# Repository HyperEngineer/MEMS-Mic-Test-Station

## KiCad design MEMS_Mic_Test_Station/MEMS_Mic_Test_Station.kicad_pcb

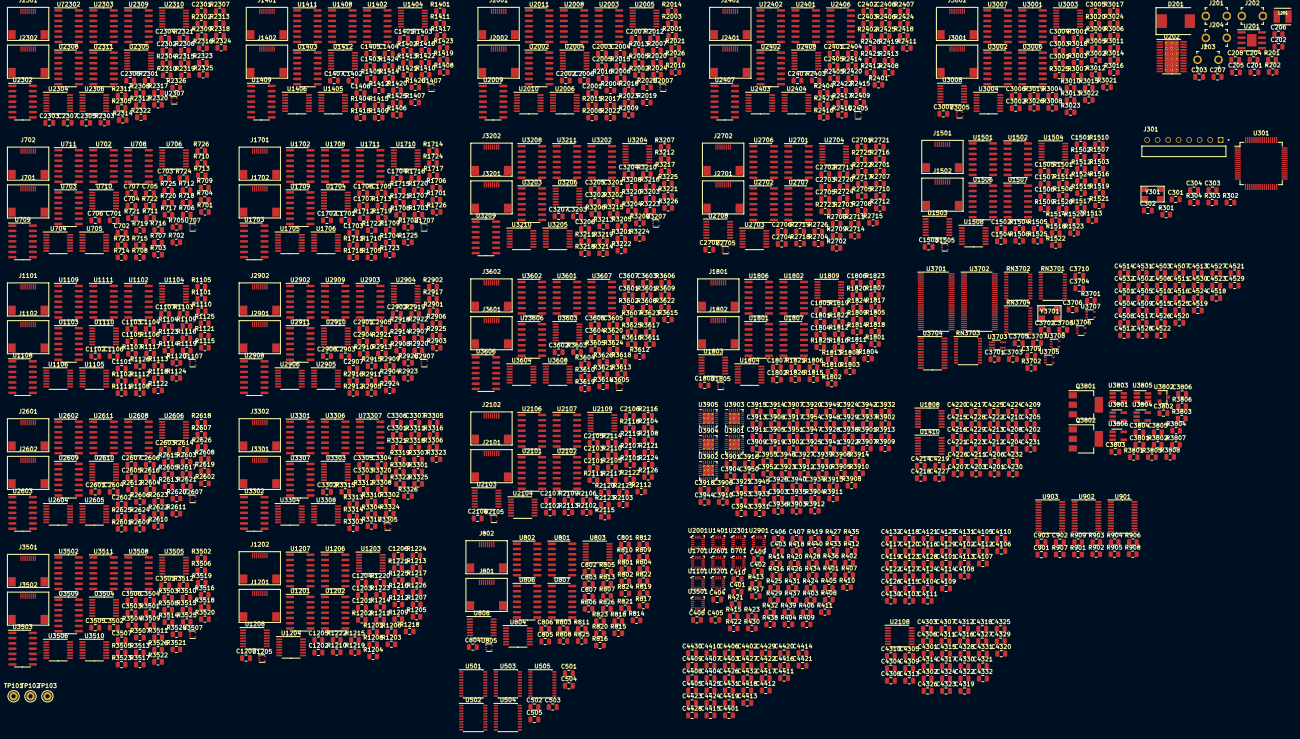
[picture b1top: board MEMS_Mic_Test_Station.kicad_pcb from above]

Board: 2 copper layers, 1286 parts (0 on the bottom side), 1034 nets, no tracks yet.

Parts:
C201: .1uF; C_0805_2012Metric
C202, C701, C703, C704, C706, C801, C803, C804, C806, C1101, C1103, C1104, C1106, C1201, C1203, C1204, C1206, C1401, C1403, C1404, C1406, C1501, C1503, C1504, C1506, C1701, C1703, C1704, C1706, C1801, C1803, C1804, C1806, C2001, C2003, C2004, C2006, C2101, C2103, C2104, C2106, C2301, C2303, C2304, C2306, C2401, C2403, C2404, C2406, C2601, C2603, C2604, C2606, C2701, C2703, C2704, C2706, C2901, C2903, C2904, C2906, C3001, C3003, C3004, C3006, C3201, C3203, C3204, C3206, C3301, C3303, C3304, C3306, C3501, C3503, C3504, C3506, C3601, C3603, C3604, C3606, C3901, C3902, C3903, C3904, C3913, C3914, C3923, C3924, C3925, C3926, C3935, C3936, C3945, C3946, C3951: 10uF; C_0805_2012Metric
C203, C204, C208: 22uF; C_0805_2012Metric
C205, C206: 0.22uF; C_0805_2012Metric
C207: 47uF; C_0805_2012Metric
C301, C302, C303, C304, C401, C402, C403, C404, C405, C406, C407, C408, C409, C410, C501, C502, C503, C504, C505, C707, C807, C901, C902, C903, C1107, C1207, C1407, C1507, C1707, C1807, C2007, C2107, C2307, C2407, C2607, C2707, C2907, C3007, C3207, C3307, C3507, C3607, C3701, C3702, C3703, C3704, C3705, C3706, C3707, C3708, C3709, C3710, C3802, C3806, C4101, C4102, C4103, C4104, C4105, C4106, C4107, C4108, C4109, C4110, C4111, C4112, C4113, C4114, C4115, C4116, C4117, C4118, C4119, C4120, C4121, C4122, C4123, C4124, C4125, C4126, C4127, C4128, C4129, C4130, C4131, C4132, C4201, C4202, C4203, C4204, C4205, C4206, C4207, C4208, C4209, C4210, C4211, C4212, C4213, C4214, C4215, C4216, C4217, C4218, C4219, C4220, C4221, C4222, C4223, C4224, C4225, C4226, C4227, C4228, C4229, C4230, C4231, C4232, C4301, C4302, C4303, C4304, C4305, C4306, C4307, C4308, C4309, C4310, C4311, C4312, C4313, C4314, C4315, C4316, C4317, C4318, C4319, C4320, C4321, C4322, C4323, C4324, C4325, C4326, C4327, C4328, C4329, C4330, C4331, C4332, C4401, C4402, C4403, C4404, C4405, C4406, C4407, C4408, C4409, C4410, C4411, C4412, C4413, C4414, C4415, C4416, C4417, C4418, C4419, C4420, C4421, C4422, C4423, C4424, C4425, C4426, C4427, C4428, C4429, C4430, C4431, C4432, C4501, C4502, C4503, C4504, C4505, C4506, C4507, C4508, C4509, C4510, C4511, C4512, C4513, C4514, C4515, C4516, C4517, C4518, C4519, C4520, C4521, C4522, C4523, C4524, C4525, C4526, C4527, C4528, C4529, C4530, C4531, C4532: 100nF; C_0805_2012Metric
C702, C705, C802, C805, C1102, C1105, C1202, C1205, C1402, C1405, C1502, C1505, C1702, C1705, C1802, C1805, C2002, C2005, C2102, C2105, C2302, C2305, C2402, C2405, C2602, C2605, C2702, C2705, C2902, C2905, C3002, C3005, C3202, C3205, C3302, C3305, C3502, C3505, C3602, C3605: 47pF; C_0805_2012Metric
C3801, C3805: 4.7uF; C_0805_2012Metric
C3803, C3804: 100pF; C_0805_2012Metric
C3905, C3906, C3917, C3918, C3919, C3920, C3921, C3922, C3927, C3928, C3939, C3940, C3941, C3942, C3943, C3944, C3947, C3953, C3954, C3955: 1uF; C_0805_2012Metric
C3907, C3908, C3909, C3910, C3911, C3912, C3915, C3916, C3929, C3930, C3931, C3932, C3933, C3934, C3937, C3938, C3948, C3949, C3950, C3952: 0.1uF; C_0805_2012Metric
D201: B330; D_SMC
J201, J202: 105-1102-001; Test_Jack_Horiz
J203, J204: 105-1103-001; Test_Jack_Horiz
J301: TSW-108-09-G-S-RA; SAMTEC_TSW-108-09-G-S-RA
J701, J702, J801, J802, J1101, J1102, J1201, J1202, J1401, J1402, J1501, J1502, J1701, J1702, J1801, J1802, J2001, J2002, J2101, J2102, J2301, J2302, J2401, J2402, J2601, J2602, J2701, J2702, J2901, J2902, J3001, J3002, J3201, J3202, J3301, J3302, J3501, J3502, J3601, J3602: Conn_01x08_0.5mm_Female_Kyocera; Kyocera_6288
L201: 6.8uH; IND_LQH44NN6R8K03L
Q3801, Q3802: PZT3904; SOT-223-3_TabPin2
R201: 100K; R_0805_2012Metric
R202: 250K; R_0805_2012Metric
R301, R302: 0; R_0805_2012Metric
R303: 10M; R_0805_2012Metric
R304, R401, R402, R403, R404, R409, R410, R411, R412, R413, R414, R415, R416, R417, R418, R419, R420, R425, R426, R427, R428, R429, R430, R431, R432, R433, R434, R437, R438, R439, R440, R901, R902, R904, R905, R907, R908, R3701, R3702, R3901, R3902, R3903, R3904, R3907, R3908, R3909, R3910, R3913, R3914: 4.7K; R_0805_2012Metric
R405, R406, R407, R408, R421, R422, R423, R424, R435, R436, R903, R906, R909, R3803, R3808, R3905, R3906, R3911, R3912, R3915: 10K; R_0805_2012Metric
R701, R715, R801, R815, R1101, R1115, R1201, R1215, R1401, R1415, R1501, R1515, R1701, R1715, R1801, R1815, R2001, R2015, R2101, R2115, R2301, R2315, R2401, R2415, R2601, R2615, R2701, R2715, R2901, R2915, R3001, R3015, R3201, R3215, R3301, R3315, R3501, R3515, R3601, R3615: 10Ω; R_0805_2012Metric
R702, R703, R708, R710, R711, R712, R713, R714, R716, R721, R723, R724, R725, R726, R802, R803, R808, R810, R811, R812, R813, R814, R816, R821, R823, R824, R825, R826, R1102, R1103, R1108, R1110, R1111, R1112, R1113, R1114, R1116, R1121, R1123, R1124, R1125, R1126, R1202, R1203, R1208, R1210, R1211, R1212, R1213, R1214, R1216, R1221, R1223, R1224, R1225, R1226, R1402, R1403, R1408, R1410, R1411, R1412, R1413, R1414, R1416, R1421, R1423, R1424, R1425, R1426, R1502, R1503, R1508, R1510, R1511, R1512, R1513, R1514, R1516, R1521, R1523, R1524, R1525, R1526, R1702, R1703, R1708, R1710, R1711, R1712, R1713, R1714, R1716, R1721, R1723, R1724, R1725, R1726, R1802, R1803, R1808, R1810, R1811, R1812, R1813, R1814, R1816, R1821, R1823, R1824, R1825, R1826, R2002, R2003, R2008, R2010, R2011, R2012, R2013, R2014, R2016, R2021, R2023, R2024, R2025, R2026, R2102, R2103, R2108, R2110, R2111, R2112, R2113, R2114, R2116, R2121, R2123, R2124, R2125, R2126, R2302, R2303, R2308, R2310, R2311, R2312, R2313, R2314, R2316, R2321, R2323, R2324, R2325, R2326, R2402, R2403, R2408, R2410, R2411, R2412, R2413, R2414, R2416, R2421, R2423, R2424, R2425, R2426, R2602, R2603, R2608, R2610, R2611, R2612, R2613, R2614, R2616, R2621, R2623, R2624, R2625, R2626, R2702, R2703, R2708, R2710, R2711, R2712, R2713, R2714, R2716, R2721, R2723, R2724, R2725, R2726, R2902, R2903, R2908, R2910, R2911, R2912, R2913, R2914, R2916, R2921, R2923, R2924, R2925, R2926, R3002, R3003, R3008, R3010, R3011, R3012, R3013, R3014, R3016, R3021, R3023, R3024, R3025, R3026, R3202, R3203, R3208, R3210, R3211, R3212, R3213, R3214, R3216, R3221, R3223, R3224, R3225, R3226, R3302, R3303, R3308, R3310, R3311, R3312, R3313, R3314, R3316, R3321, R3323, R3324, R3325, R3326, R3502, R3503, R3508, R3510, R3511, R3512, R3513, R3514, R3516, R3521, R3523, R3524, R3525, R3526, R3602, R3603, R3608, R3610, R3611, R3612, R3613, R3614, R3616, R3621, R3623, R3624, R3625, R3626: 100KΩ; R_0805_2012Metric
R704, R709, R717, R722, R804, R809, R817, R822, R1104, R1109, R1117, R1122, R1204, R1209, R1217, R1222, R1404, R1409, R1417, R1422, R1504, R1509, R1517, R1522, R1704, R1709, R1717, R1722, R1804, R1809, R1817, R1822, R2004, R2009, R2017, R2022, R2104, R2109, R2117, R2122, R2304, R2309, R2317, R2322, R2404, R2409, R2417, R2422, R2604, R2609, R2617, R2622, R2704, R2709, R2717, R2722, R2904, R2909, R2917, R2922, R3004, R3009, R3017, R3022, R3204, R3209, R3217, R3222, R3304, R3309, R3317, R3322, R3504, R3509, R3517, R3522, R3604, R3609, R3617, R3622: 10KΩ; R_0805_2012Metric
R705, R718, R805, R818, R1105, R1118, R1205, R1218, R1405, R1418, R1505, R1518, R1705, R1718, R1805, R1818, R2005, R2018, R2105, R2118, R2305, R2318, R2405, R2418, R2605, R2618, R2705, R2718, R2905, R2918, R3005, R3018, R3205, R3218, R3305, R3318, R3505, R3518, R3605, R3618: 11KΩ; R_0805_2012Metric
R706, R707, R720, R806, R807, R820, R1106, R1107, R1120, R1206, R1207, R1220, R1406, R1407, R1420, R1506, R1507, R1520, R1706, R1707, R1720, R1806, R1807, R1820, R2006, R2007, R2020, R2106, R2107, R2120, R2306, R2307, R2320, R2406, R2407, R2420, R2606, R2607, R2620, R2706, R2707, R2720, R2906, R2907, R2920, R3006, R3007, R3020, R3206, R3207, R3220, R3306, R3307, R3320, R3506, R3507, R3520, R3606, R3607, R3620: 200KΩ; R_0805_2012Metric
R719, R819, R1119, R1219, R1419, R1519, R1719, R1819, R2019, R2119, R2319, R2419, R2619, R2719, R2919, R3019, R3219, R3319, R3519, R3619: 200K; R_0805_2012Metric
R3801, R3806: 470; R_0805_2012Metric
R3802, R3805: 1K; R_0805_2012Metric
R3804, R3807: 2K; R_0805_2012Metric
RN3701, RN3702, RN3703, RN3704: VTSR2003101; SSOP-20_4.4x6.5mm_P0.65mm
TP101, TP102, TP103: dk_Test-Points_5000; Test_Point_D1.02mm
U201: ADP2302ARDZ; SOIC-8-1EP_3.9x4.9mm_P1.27mm_EP2.29x3mm
U202: TPS70351; HTSSOP-24-1EP_4.4x7.8mm_P0.65mm_EP3.4x7.8mm_Mask2.4x4.68mm_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
U301: PIC32MZ2048EFM064-TQFP; TQFP-64_10x10mm_P0.5mm
U501, U502, U503, U504, U505: 74VHC9273PW; SSOP-20_4.4x6.5mm_P0.65mm
U701, U1101, U1401, U1701, U2001, U2301, U2601, U2901, U3201, U3501: PAC195X-1; VQFN-16_3x3mm
U702, U703, U708, U709, U711, U801, U802, U806, U807, U1102, U1103, U1108, U1109, U1111, U1201, U1202, U1206, U1207, U1402, U1403, U1408, U1409, U1411, U1501, U1502, U1506, U1507, U1702, U1703, U1708, U1709, U1711, U1801, U1802, U1806, U1807, U2002, U2003, U2008, U2009, U2011, U2101, U2102, U2106, U2107, U2302, U2303, U2308, U2309, U2311, U2401, U2402, U2406, U2407, U2602, U2603, U2608, U2609, U2611, U2701, U2702, U2706, U2707, U2902, U2903, U2908, U2909, U2911, U3001, U3002, U3006, U3007, U3202, U3203, U3208, U3209, U3211, U3301, U3302, U3306, U3307, U3502, U3503, U3508, U3509, U3511, U3601, U3602, U3606, U3607: 74LV4066; SOIC-14_3.9x8.7mm_P1.27mm
U704, U803, U1104, U1203, U1404, U1503, U1704, U1803, U2004, U2103, U2304, U2403, U2604, U2703, U2904, U3003, U3204, U3303, U3504, U3603: 74LV14PW; TSSOP-14_4.4x5mm_P0.65mm
U705, U710, U804, U808, U1105, U1110, U1204, U1208, U1405, U1410, U1412, U1504, U1508, U1705, U1710, U1804, U1808, U1809, U2005, U2010, U2104, U2108, U2109, U2305, U2310, U2404, U2408, U2605, U2610, U2704, U2708, U2905, U2910, U3004, U3008, U3205, U3210, U3304, U3308, U3505, U3510, U3604, U3608: 74LVC08APW; TSSOP-14_4.4x5mm_P0.65mm
U706, U1106, U1406, U1706, U2006, U2306, U2606, U2906, U3206, U3506: LMV324A; TSSOP-14_4.4x5mm_P0.65mm
U707, U805, U1107, U1205, U1407, U1505, U1707, U1805, U2007, U2105, U2307, U2405, U2607, U2705, U2907, U3005, U3207, U3305, U3507, U3605: 74LVC1G04; SOT-553
U901, U902, U903: TCA9548APWR; TSSOP-24_4.4x7.8mm_P0.65mm
U3701: 74AVC20T245DGG; TSSOP-56_6.1x14mm_P0.5mm
U3702: 74AVC20T245; TSSOP-56_6.1x14mm_P0.5mm
U3703: 74LVC1G04; SOT-353_SC-70-5_Handsoldering
U3704: CDCE949QPWRQ1; TSSOP-24_4.4x7.8mm_P0.65mm
U3705, U3706, U3707, U3708: 74LVC1G126; SOT-353_SC-70-5
U3801, U3804, U3806: LMV931MG; SOT-23-5_HandSoldering
U3802: REF3040; SOT-23
U3803, U3805: DAC121S101QCMK; SOT-23-6_Handsoldering
U3901, U3902, U3903, U3904, U3905: PCMD3180; QFN-24-1EP_4x4mm_P0.5mm_EP2.7x2.7mm_ThermalVias
U?2302, U?2402, U?3307, U?3606: 74LV4066; SOIC-14_3.9x8.7mm_P1.27mm
Y301, Y3701: 27MHz; ECX-53B-DU

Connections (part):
+1V8: C207.1, C3702.1, C3706.1, U202.14, U202.15, U202.16, U3704.3, U3704.13
+3V3: C208.1, C301.1, C401.1, C402.1, C403.1, C404.1, C405.1, C406.1, C407.1, C408.1, C409.1, C410.1, C707.1, C807.1, C1107.1, C1207.1, C1407.1, C1507.1, C1707.1, C1807.1, C2007.1, C2107.1, C2307.1, C2407.1, C2607.1, C2707.1, C2907.1, C3007.1, C3207.1, C3307.1, C3507.1, C3607.1, C3701.1, C3703.1, C3704.1, C3705.1, C3707.1, C3708.1, C3709.1, C3710.1, C3902.1, C3904.1, C3905.1, C3906.1, C3908.1, C3910.1, C3911.1, C3912.1, C3924.1, C3926.1, C3927.1, C3928.1, C3930.1, C3932.1, C3933.1, C3934.1, C3946.1, C3947.1, C3949.1, C3950.1, C4101.1, C4102.1, C4103.1, C4104.1, C4105.1, C4106.1, C4107.1, C4108.1, C4109.1, C4110.1, C4111.1, C4112.1, C4113.1, C4114.1, C4115.1, C4116.1, C4117.1, C4118.1, C4119.1, C4120.1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
+5V: C203.2, C204.2, C205.1, C206.1, L201.2, Q3801.2, Q3802.2, U201.5, U202.2, U202.3, U202.6, U202.10, U202.11, U3801.5, U3802.1, U3804.5, U3806.5
+6V: C202.1, J201.1, J202.1, R201.2, U201.2, U201.3
/1Q1: U501.3, U501.19, U705.4, U705.9
/1Q2: U501.4, U501.18, U710.4, U710.9
/1Q3: U501.5, U501.17, U804.4, U804.9
/1Q4: U501.6, U501.16, U808.4, U808.9
/1Q5: U501.7, U501.15, U1208.4, U1208.9
/1Q6: U501.8, U501.14, U1204.4, U1204.9
/1Q7: U501.9, U501.13, U1105.4, U1105.9
/1Q8: U501.12, U502.2, U1110.4, U1110.9
/2Q1: U502.3, U502.19, U1405.4, U1405.9, U1508.4, U1508.9
/2Q2: U502.4, U502.18, U1504.4, U1504.9
/2Q3: U502.5, U502.17
/2Q4: U502.6, U502.16, U1412.4, U1412.9
/2Q5: U502.7, U502.15, U1809.4, U1809.9
/2Q6: U502.8, U502.14, U1804.4, U1804.9
/2Q7: U502.9, U502.13, U1705.4, U1705.9
/2Q8: U502.12, U503.2, U1710.4, U1710.9
/2WA0: U301.13, U901.1, U902.1, U903.1
/2WA1: U301.12, U901.2, U902.2, U903.2
/2WA2: U301.11, U901.21, U902.21, U903.21
/2WA3: R903.2, U301.17, U901.3
/2WA4: R909.2, U301.18, U903.3
/2WA5: R906.2, U301.21, U902.3
/3Q1: U503.3, U503.19, U2109.4, U2109.9
/3Q2: U503.4, U503.18, U2104.4, U2104.9
/3Q3: U503.5, U503.17, U2005.4, U2005.9
/3Q4: U503.6, U503.16, U2010.4, U2010.9
/3Q5: U503.7, U503.15, U2408.4, U2408.9
/3Q6: U503.8, U503.14, U2404.4, U2404.9
/3Q7: U503.9, U503.13, U2305.4, U2305.9
/3Q8: U503.12, U504.2, U2310.4, U2310.9
/4Q1: U504.3, U504.19, U2708.4, U2708.9
/4Q2: U504.4, U504.18, U2704.4, U2704.9
/4Q3: U504.5, U504.17, U2605.4, U2605.9
/4Q4: U504.6, U504.16, U2610.4, U2610.9
/4Q5: U504.7, U504.15, U3008.4, U3008.9
/4Q6: U504.8, U504.14, U3004.4, U3004.9
/4Q7: U504.9, U504.13, U2905.4, U2905.9
/4Q8: U504.12, U505.2, U2910.4, U2910.9
/5Q1: U505.3, U505.19, U3308.4, U3308.9
/5Q2: U505.4, U505.18, U3304.4, U3304.9
/5Q3: U505.5, U505.17, U3205.4, U3205.9
/5Q4: U505.6, U505.16, U3210.4, U3210.9
/5Q5: U505.7, U505.15, U3608.4, U3608.9
/5Q6: U505.8, U505.14, U3604.4, U3604.9
/5Q7: U505.9, U505.13, U3505.4, U3505.9
/5Q8: U505.12, U3510.4, U3510.9
/AO: U301.14, U711.2, U711.3, U711.9, U711.10, U1111.2, U1111.3, U1111.9, U1111.10, U1411.2, U1411.3, U1411.9, U1411.10, U1711.2, U1711.3, U1711.9, U1711.10, U2011.2, U2011.3, U2011.9, U2011.10, U2311.2, U2311.3, U2311.9, U2311.10, U2611.2, U2611.3, U2611.9, U2611.10, U2911.2, U2911.3, U2911.9, U2911.10, U3211.2, U3211.3, U3211.9, U3211.10, U3511.2, U3511.3, U3511.9, U3511.10
/CA1: RN3701.20, U702.4, U3901.7
/CA2: RN3701.19, U708.4
/CA3: RN3701.18, U801.4, U3901.9
/CA4: RN3701.17, U806.4
/CA5: RN3701.16, U1102.4, U3901.11
/CA6: RN3701.15, U1108.4
/CA7: RN3701.14, U1201.4, U3901.13
/CA8: RN3701.13, U1206.4
/CA9: RN3701.12, U1402.4, U3903.7
/CA10: RN3701.11, U1408.4
/CB1: RN3703.20, U1501.4, U3903.9
/CB2: RN3703.19, U1506.4
/CB3: RN3703.18, U1702.4, U3903.11
/CB4: RN3703.17, U1708.4
/CB5: RN3703.16, U1801.4, U3903.13
/CB6: RN3703.15, U1806.4
/CB7: RN3703.14, U2002.4, U3905.7
/CB8: RN3703.13, U2008.4
/CB9: RN3703.12, U2101.4, U3905.9
/CB10: RN3703.11, U2106.4
/CC1: RN3702.20, U2302.4, U3905.11
/CC2: RN3702.19, U2308.4
/CC3: RN3702.18, U2401.4, U3905.13
/CC4: RN3702.17, U2406.4
/CC5: RN3702.16, U2602.4, U3902.7
/CC6: RN3702.15, U2608.4
/CC7: RN3702.14, U2701.4, U3902.9
/CC8: RN3702.13, U2706.4
/CC9: RN3702.12, U2902.4, U3902.11
/CC10: RN3702.11, U2908.4
/CD1: RN3704.20, U3001.4, U3902.13
/CD2: RN3704.19, U3006.4
/CD3: RN3704.18, U3202.4, U3904.7
/CD4: RN3704.17, U3208.4
/CD5: RN3704.16, U3301.4, U3904.9
/CD6: RN3704.15, U3306.4
/CD7: RN3704.14, U3502.4, U3904.11
/CD8: RN3704.13, U3508.4
/CD9: RN3704.12, U3601.4, U3904.13
/CD10: RN3704.11, U3606.4
/CE: R711.2, R724.2, R811.2, R824.2, R1111.2, R1124.2, R1211.2, R1224.2, R1411.2, R1424.2, R1511.2, R1524.2, R1711.2, R1724.2, R1811.2, R1824.2, R2011.2, R2024.2, R2111.2, R2124.2, R2311.2, R2324.2, R2411.2, R2424.2, R2611.2, R2624.2, R2711.2, R2724.2, R2911.2, R2924.2, R3011.2, R3024.2, R3211.2, R3224.2, R3311.2, R3324.2, R3511.2, R3524.2, R3611.2, R3624.2, U301.47, U702.5, U708.5, U801.5, U806.5, U1102.5, U1108.5, U1201.5, U1206.5, U1402.5, U1408.5, U1501.5, U1506.5, U1702.5, U1708.5, U1801.5, U1806.5, U2002.5, U2008.5, U2101.5, U2106.5, U2302.5, U2308.5, U2401.5, U2406.5, U2602.5, U2608.5, U2701.5, U2706.5, U2902.5, U2908.5, U3001.5, U3006.5, U3202.5, U3208.5, U3301.5, U3306.5, U3502.5, U3508.5, U3601.5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
/CKSC: R3702.1, U903.11, U3704.22
/CKSD: R3701.1, U903.10, U3704.23
/Clock_Source/1A1: RN3701.1, U3701.55
/Clock_Source/1A2: RN3701.2, U3701.54
/Clock_Source/1A3: RN3701.3, U3701.52
/Clock_Source/1A4: RN3701.4, U3701.51
/Clock_Source/1A5: RN3701.5, U3701.49
/Clock_Source/1A6: RN3701.6, U3701.48
/Clock_Source/1A7: RN3701.7, U3701.47
/Clock_Source/1A8: RN3701.8, U3701.45
/Clock_Source/1A9: RN3701.9, U3701.44
/Clock_Source/1AA: RN3701.10, U3701.43
/Clock_Source/2A1: RN3703.1, U3701.42
/Clock_Source/2A2: RN3703.2, U3701.41
/Clock_Source/2A3: RN3703.3, U3701.40
/Clock_Source/2A4: RN3703.4, U3701.38
/Clock_Source/2A5: RN3703.5, U3701.37
/Clock_Source/2A6: RN3703.6, U3701.36
/Clock_Source/2A7: RN3703.7, U3701.34
/Clock_Source/2A8: RN3703.8, U3701.33
/Clock_Source/2A9: RN3703.9, U3701.31
/Clock_Source/2AA: RN3703.10, U3701.30
/Clock_Source/3A1: RN3702.1, U3702.55
/Clock_Source/3A2: RN3702.2, U3702.54
/Clock_Source/3A3: RN3702.3, U3702.52
/Clock_Source/3A4: RN3702.4, U3702.51
/Clock_Source/3A5: RN3702.5, U3702.49
/Clock_Source/3A6: RN3702.6, U3702.48
/Clock_Source/3A7: RN3702.7, U3702.47
/Clock_Source/3A8: RN3702.8, U3702.45
/Clock_Source/3A9: RN3702.9, U3702.44
/Clock_Source/3A10: RN3702.10, U3702.43
/Clock_Source/4A1: RN3704.1, U3702.42
/Clock_Source/4A2: RN3704.2, U3702.41
/Clock_Source/4A3: RN3704.3, U3702.40
/Clock_Source/4A4: RN3704.4, U3702.38
/Clock_Source/4A5: RN3704.5, U3702.37
/Clock_Source/4A6: RN3704.6, U3702.36
/Clock_Source/4A7: RN3704.7, U3702.34
/Clock_Source/4A8: RN3704.8, U3702.33
/Clock_Source/4A9: RN3704.9, U3702.31
/Clock_Source/4A10: RN3704.10, U3702.30
/Clock_Source/MIC_CLK_A: U3701.2, U3701.3, U3701.5, U3701.6, U3701.8, U3701.9, U3701.10, U3701.12, U3701.13, U3701.14, U3705.4
/Clock_Source/MIC_CLK_B: U3701.15, U3701.16, U3701.17, U3701.19, U3701.20, U3701.21, U3701.23, U3701.24, U3701.26, U3701.27, U3706.4
/Clock_Source/MIC_CLK_C: U3702.2, U3702.3, U3702.5, U3702.6, U3702.8, U3702.9, U3702.10, U3702.12, U3702.13, U3702.14, U3707.4
/Clock_Source/MIC_CLK_D: U3702.15, U3702.16, U3702.17, U3702.19, U3702.20, U3702.21, U3702.23, U3702.24, U3702.26, U3702.27, U3708.4
/DIN1: U301.46, U3803.4
/DIN2: U301.23, U3805.4
/DO: U301.48, U703.9, U709.9, U802.9, U807.9, U1103.9, U1109.9, U1202.9, U1207.9, U1403.9, U1409.9, U1502.9, U1507.9, U1703.9, U1709.9, U1802.9, U1807.9, U2003.9, U2009.9, U2102.9, U2107.9, U2303.9, U2309.9, U2402.9, U2407.9, U2603.9, U2609.9, U2702.9, U2707.9, U2903.9, U2909.9, U3002.9, U3007.9, U3203.9, U3209.9, U3302.9, U3307.9, U3503.9, U3509.9, U3602.9, U3607.9
/DVE: R703.1, R716.1, R803.1, R816.1, R1103.1, R1116.1, R1203.1, R1216.1, R1403.1, R1416.1, R1503.1, R1516.1, R1703.1, R1716.1, R1803.1, R1816.1, R2003.1, R2016.1, R2103.1, R2116.1, R2303.1, R2316.1, R2403.1, R2416.1, R2603.1, R2616.1, R2703.1, R2716.1, R2903.1, R2916.1, R3003.1, R3016.1, R3203.1, R3216.1, R3303.1, R3316.1, R3503.1, R3516.1, R3603.1, R3616.1, U301.58, U703.13, U704.1, U704.9, U709.13, U802.13, U803.1, U803.9, U807.13, U1103.13, U1104.1, U1104.9, U1109.13, U1202.13, U1203.1, U1203.9, U1207.13, U1403.13, U1404.1, U1404.9, U1409.13, U1502.13, U1503.1, U1503.9, U1507.13, U1703.13, U1704.1, U1704.9, U1709.13, U1802.13, U1803.1, U1803.9, U1807.13, U2003.13, U2004.1, U2004.9, U2009.13, U2102.13, U2103.1, U2103.9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
/I2S: U301.5, U3901.21, U3902.21, U3903.21, U3904.21, U3905.21
/Init: U301.63, U501.2
/MC1: R409.2, U701.4, U901.5
/MC2: R411.2, U901.7, U1101.4
/MC3: C403.2, R413.2, U901.9, U1401.4
/MC4: R415.2, U901.11, U1701.4
/MC5: R425.2, U901.14, U2001.4
/MC6: R427.2, U901.16, U2301.4
/MC7: R429.2, U901.18, U2601.4
/MC8: R431.2, U903.5, U2901.4
/MC9: R437.2, U903.7, U3201.4
/MC10: R439.2, U903.9, U3501.4
/MDC: U301.4, U301.49, U3703.4, U3901.22, U3902.22, U3903.22, U3904.22, U3905.22
/MS1: R410.2, U701.5, U901.4
/MS2: R412.2, U901.6, U1101.5
/MS3: R414.2, U901.8, U1401.5
/MS4: R416.2, U901.10, U1701.5
/MS5: R426.2, U901.13, U2001.5
/MS6: R428.2, U901.15, U2301.5
/MS7: R430.2, U901.17, U2601.5
/MS8: R432.2, U903.4, U2901.5
/MS9: R438.2, U903.6, U3201.5
/MS10: R440.2, U903.8, U3501.5
/MSC: R902.2, U301.51, U901.22
/MSD: R901.2, U301.50, U901.23
/Microcontroller/PGC: J301.05, U301.15
/Microcontroller/PGD: J301.04, U301.16
/Microcontroller/U1RX: TP103.1, U301.57
/Microcontroller/U1TX: TP102.1, U301.56
/Microcontroller/~MCLR: C304.1, J301.01, R301.1, R304.2, U301.9
/NE: R712.2, R725.2, R812.2, R825.2, R1112.2, R1125.2, R1212.2, R1225.2, R1412.2, R1425.2, R1512.2, R1525.2, R1712.2, R1725.2, R1812.2, R1825.2, R2012.2, R2025.2, R2112.2, R2125.2, R2312.2, R2325.2, R2412.2, R2425.2, R2612.2, R2625.2, R2712.2, R2725.2, R2912.2, R2925.2, R3012.2, R3025.2, R3212.2, R3225.2, R3312.2, R3325.2, R3512.2, R3525.2, R3612.2, R3625.2, U301.3, U702.6, U708.6, U801.6, U806.6, U1102.6, U1108.6, U1201.6, U1206.6, U1402.6, U1408.6, U1501.6, U1506.6, U1702.6, U1708.6, U1801.6, U1806.6, U2002.6, U2008.6, U2101.6, U2106.6, U2308.6, U2401.6, U2406.6, U2602.6, U2608.6, U2701.6, U2706.6, U2902.6, U2908.6, U3001.6, U3006.6, U3202.6, U3208.6, U3301.6, U3306.6, U3502.6, U3508.6, U3601.6, U?2302.6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
/PC1: R3901.2, U903.14, U3901.17
/PC2: R3907.2, U903.16, U3903.17
/PC3: R3913.2, U903.18, U3905.17
/PC4: R3902.2, U902.5, U3902.17
/PC5: R3908.2, U902.7, U3904.17
/PE: R708.1, R721.1, R808.1, R821.1, R1108.1, R1121.1, R1208.1, R1221.1, R1408.1, R1421.1, R1508.1, R1521.1, R1708.1, R1721.1, R1808.1, R1821.1, R2008.1, R2021.1, R2108.1, R2121.1, R2308.1, R2321.1, R2408.1, R2421.1, R2608.1, R2621.1, R2708.1, R2721.1, R2908.1, R2921.1, R3008.1, R3021.1, R3208.1, R3221.1, R3308.1, R3321.1, R3508.1, R3521.1, R3608.1, R3621.1, U301.1, U702.13, U708.13, U801.13, U806.13, U1102.13, U1108.13, U1201.13, U1206.13, U1402.13, U1408.13, U1501.13, U1506.13, U1702.13, U1708.13, U1801.13, U1806.13, U2002.13, U2008.13, U2101.13, U2106.13, U2302.13, U2308.13, U2401.13, U2406.13, U2602.13, U2608.13, U2701.13, U2706.13, U2902.13, U2908.13, U3001.13, U3006.13, U3202.13, U3208.13, U3301.13, U3306.13, U3502.13, U3508.13, U3601.13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
/PO1: U703.10, U709.10, U3901.6
/PO2: U802.10, U807.10, U3901.8
/PO3: U1103.10, U1109.10, U3901.10
/PO4: U1202.10, U1207.10, U3901.12
/PO5: U1403.10, U1409.10, U3903.6
/PO6: U1502.10, U1507.10, U3903.8
/PO7: U1703.10, U1709.10, U3903.10
/PO8: U1802.10, U1807.10, U3903.12
/PO9: U2003.10, U2009.10, U3905.6
/PO10: U2102.10, U2107.10, U3905.8
/PO11: U2303.10, U2309.10, U3905.10
/PO12: U2402.10, U2407.10, U3905.12
/PO13: U2603.10, U2609.10, U3902.6
/PO14: U2702.10, U2707.10, U3902.8
/PO15: U2903.10, U2909.10, U3902.10
/PO16: U3002.10, U3007.10, U3902.12
/PO17: U3203.10, U3209.10, U3904.6
/PO18: U3302.10, U3307.10, U3904.8
/PO19: U3503.10, U3509.10, U3904.10
/PO20: U3602.10, U3607.10, U3904.12
/PS1: R3903.2, U903.13, U3901.18
/PS2: R3909.2, U903.15, U3903.18
/PS3: R3914.2, U903.17, U3905.18
/PS4: R3904.2, U902.4, U3902.18
/PS5: R3910.2, U902.6, U3904.18
/RCK: U301.61, U501.11, U502.11, U503.11, U504.11, U505.11
/SCK1: U301.44, U3803.5
/SCK2: U301.29, U3805.5
/SG: R713.1, R726.1, R813.1, R826.1, R1113.1, R1126.1, R1213.1, R1226.1, R1413.1, R1426.1, R1513.1, R1526.1, R1713.1, R1726.1, R1813.1, R1826.1, R2013.1, R2026.1, R2113.1, R2126.1, R2313.1, R2326.1, R2413.1, R2426.1, R2613.1, R2626.1, R2713.1, R2726.1, R2913.1, R2926.1, R3013.1, R3026.1, R3213.1, R3226.1, R3313.1, R3326.1, R3513.1, R3526.1, R3613.1, R3626.1, U301.64, U702.12, U708.12, U801.12, U806.12, U1102.12, U1108.12, U1201.12, U1206.12, U1402.12, U1408.12, U1501.12, U1506.12, U1702.12, U1708.12, U1801.12, U1806.12, U2002.12, U2008.12, U2101.12, U2106.12, U2302.12, U2308.12, U2401.12, U2406.12, U2602.12, U2608.12, U2701.12, U2706.12, U2902.12, U2908.12, U3001.12, U3006.12, U3202.12, U3208.12, U3301.12, U3306.12, U3502.12, U3508.12, U3601.12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
/SYN1: U301.43, U3803.6
/SYN2: U301.30, U3805.6
/Sel: J701.6, J801.6, J1101.6, J1201.6, J1401.6, J1501.6, J1701.6, J1801.6, J2001.6, J2101.6, J2301.6, J2401.6, J2601.6, J2701.6, J2901.6, J3001.6, J3201.6, J3301.6, J3501.6, J3601.6, U301.10, U301.52, U707.2, U805.2, U1107.2, U1205.2, U1407.2, U1505.2, U1707.2, U1805.2, U2007.2, U2105.2, U2307.2, U2405.2, U2607.2, U2705.2, U2907.2, U3005.2, U3207.2, U3305.2, U3507.2, U3605.2, U3901.23, U3902.23, U3903.23, U3904.23, U3905.23
/Ty: U301.2, U704.5, U704.13, U705.12, U710.12, U803.5, U803.13, U804.12, U808.12, U1104.5, U1104.13, U1105.12, U1110.12, U1203.5, U1203.13, U1204.12, U1208.12, U1404.5, U1404.13, U1405.12, U1412.12, U1503.5, U1503.13, U1504.12, U1508.12, U1704.5, U1704.13, U1705.12, U1710.12, U1803.5, U1803.13, U1804.12, U1809.12, U2004.5, U2004.13, U2005.12, U2010.12, U2103.5, U2103.13, U2104.12, U2109.12, U2304.5, U2304.13, U2305.12, U2310.12, U2403.5, U2403.13, U2404.12, U2408.12, U2604.5, U2604.13, U2605.12, U2610.12, U2703.5, U2703.13, U2704.12, U2708.12, U2904.5, U2904.13, U2905.12, U2910.12, U3003.5, U3003.13, U3004.12, U3008.12, U3204.5, U3204.13, U3205.12, U3210.12, U3303.5, U3303.13, U3304.12, U3308.12, U3504.5, U3504.13, U3505.12, U3510.12, U3603.5, U3603.13, U3604.12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
/VB1: C3801.1, C3802.1, Q3801.3, R701.2, R715.2, R801.2, R815.2, R1101.2, R1115.2, R1201.2, R1215.2, R1401.2, R1415.2, R1501.2, R1515.2, R1701.2, R1715.2, R1801.2, R1815.2, R2001.2, R2015.2, R2101.2, R2115.2, R2301.2, R2315.2, R2401.2, R2415.2, R2601.2, R2615.2, R2701.2, R2715.2, R2901.2, R2915.2, R3001.2, R3015.2, R3201.2, R3215.2, R3301.2, R3315.2, R3501.2, R3515.2, R3601.2, R3615.2, R3803.2, U701.8, U701.10, U701.11, U701.13, U1101.8, U1101.10, U1101.11, U1101.13, U1401.8, U1401.10, U1401.11, U1401.13, U1701.8, U1701.10, U1701.11, U1701.13, U2001.8, U2001.10, U2001.11, U2001.13, U2301.8, U2301.10, U2301.11, U2301.13, U2601.8, U2601.10, U2601.11, U2601.13, U2901.8, U2901.10, U2901.11, U2901.13, U3201.8, U3201.10, U3201.11, U3201.13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
/VB2: C3805.1, C3806.1, Q3802.3, R3808.2, U703.1, U709.1, U802.1, U807.1, U1103.1, U1109.1, U1202.1, U1207.1, U1403.1, U1409.1, U1502.1, U1507.1, U1703.1, U1709.1, U1802.1, U1807.1, U2003.1, U2009.1, U2102.1, U2107.1, U2303.1, U2309.1, U2407.1, U2603.1, U2609.1, U2702.1, U2707.1, U2903.1, U2909.1, U3002.1, U3007.1, U3203.1, U3209.1, U3302.1, U3307.1, U3503.1, U3509.1, U3602.1, U3607.1, U3806.3, U?2402.1
/VBC: U3701.35, U3701.50, U3702.35, U3702.50, U3804.3, U3804.4
/~CLR: U301.62, U501.1, U502.1, U503.1, U504.1, U505.1
/~PME: U301.53, U704.3, U704.11, U705.2, U705.13, U710.2, U710.13, U803.3, U803.11, U804.2, U804.13, U808.2, U808.13, U1104.3, U1104.11, U1105.2, U1105.13, U1110.2, U1110.13, U1203.3, U1203.11, U1204.2, U1204.13, U1208.2, U1208.13, U1404.3, U1404.11, U1405.2, U1405.13, U1412.2, U1412.13, U1503.3, U1503.11, U1504.2, U1504.13, U1508.2, U1508.13, U1704.3, U1704.11, U1705.2, U1705.13, U1710.2, U1710.13, U1803.3, U1803.11, U1804.2, U1804.13, U1809.2, U1809.13, U2004.3, U2004.11, U2005.2, U2005.13, U2010.2, U2010.13, U2103.3, U2103.11, U2104.2, U2104.13, U2109.2, U2109.13, U2304.3, U2304.11, U2305.2, U2305.13, U2310.2, U2310.13, U2403.3, U2403.11, U2404.2, U2404.13, U2408.2, U2408.13, U2604.3, U2604.11, U2605.2, U2605.13, U2610.2, U2610.13, U2703.3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
/~RST: R202.2, R301.2, U202.18
/~SCE: U301.45, U3701.29, U3701.56, U3702.29, U3702.56
GNDREF: C202.2, C203.1, C204.1, C205.2, C206.2, C207.2, C208.2, C301.2, C302.1, C303.1, C304.2, C401.2, C402.2, C404.2, C405.2, C406.2, C407.2, C408.2, C409.2, C410.2, C501.2, C502.2, C503.2, C504.2, C505.2, C702.1, C705.1, C707.2, C802.1, C805.1, C807.2, C901.2, C902.2, C903.2, C1102.1, C1105.1, C1107.2, C1202.1, C1205.1, C1207.2, C1402.1, C1405.1, C1407.2, C1502.1, C1505.1, C1507.2, C1702.1, C1705.1, C1707.2, C1802.1, C1805.1, C1807.2, C2002.1, C2005.1, C2007.2, C2102.1, C2105.1, C2107.2, C2302.1, C2305.1, C2307.2, C2402.1, C2405.1, C2407.2, C2602.1, C2605.1, C2607.2, C2702.1, C2705.1, C2707.2, C2902.1, C2905.1, C2907.2, C3002.1, C3005.1, C3007.2, C3202.1, C3205.1, C3207.2, C3302.1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
unnamed: C201.1, D201.1, L201.1, U201.8
unnamed: C201.2, U201.1
unnamed: C302.2, R302.1, R303.1, Y301.3
unnamed: C303.2, R303.2, U301.31, Y301.1
unnamed: C501.1, C502.1, C503.1, C504.1, C505.1
unnamed: C701.1, R707.2, U706.3
unnamed: C701.2, R704.1, R706.2
unnamed: C702.2, R704.2, R705.2, U702.2
unnamed: C703.1, R709.1, U702.11
unnamed: C703.2, R710.2, U702.9
unnamed: C704.1, R720.2, U706.5
unnamed: C704.2, R717.1, R719.2
unnamed: C705.2, R717.2, R718.2, U708.2
unnamed: C706.1, R722.1, U708.11
unnamed: C706.2, R723.2, U708.9
unnamed: C801.1, R807.2, U706.10
unnamed: C801.2, R804.1, R806.2
unnamed: C802.2, R804.2, R805.2, U801.2
unnamed: C803.1, R809.1, U801.11
unnamed: C803.2, R810.2, U801.9
unnamed: C804.1, R820.2, U706.12
unnamed: C804.2, R817.1, R819.2
unnamed: C805.2, R817.2, R818.2, U806.2
unnamed: C806.1, R822.1, U806.11
unnamed: C806.2, R823.2, U806.9
unnamed: C901.1, C902.1, C903.1
unnamed: C1101.1, R1107.2, U1106.3
unnamed: C1101.2, R1104.1, R1106.2
unnamed: C1102.2, R1104.2, R1105.2, U1102.2
unnamed: C1103.1, R1109.1, U1102.11
unnamed: C1103.2, R1110.2, U1102.9
unnamed: C1104.1, R1120.2, U1106.5
unnamed: C1104.2, R1117.1, R1119.2
unnamed: C1105.2, R1117.2, R1118.2, U1108.2
unnamed: C1106.1, R1122.1, U1108.11
unnamed: C1106.2, R1123.2, U1108.9
unnamed: C1201.1, R1207.2, U1106.10
unnamed: C1201.2, R1204.1, R1206.2
unnamed: C1202.2, R1204.2, R1205.2, U1201.2
unnamed: C1203.1, R1209.1, U1201.11
unnamed: C1203.2, R1210.2, U1201.9
unnamed: C1204.1, R1220.2, U1106.12
unnamed: C1204.2, R1217.1, R1219.2
unnamed: C1205.2, R1217.2, R1218.2, U1206.2
unnamed: C1206.1, R1222.1, U1206.11
unnamed: C1206.2, R1223.2, U1206.9
unnamed: C1401.1, R1407.2, U1406.3
unnamed: C1401.2, R1404.1, R1406.2
unnamed: C1402.2, R1404.2, R1405.2, U1402.2
unnamed: C1403.1, R1409.1, U1402.11
unnamed: C1403.2, R1410.2, U1402.9
unnamed: C1404.1, R1420.2, U1406.5
unnamed: C1404.2, R1417.1, R1419.2
unnamed: C1405.2, R1417.2, R1418.2, U1408.2
unnamed: C1406.1, R1422.1, U1408.11
unnamed: C1406.2, R1423.2, U1408.9
unnamed: C1501.1, R1507.2, U1406.10
unnamed: C1501.2, R1504.1, R1506.2
unnamed: C1502.2, R1504.2, R1505.2, U1501.2
unnamed: C1503.1, R1509.1, U1501.11
unnamed: C1503.2, R1510.2, U1501.9
unnamed: C1504.1, R1520.2, U1406.12
unnamed: C1504.2, R1517.1, R1519.2
unnamed: C1505.2, R1517.2, R1518.2, U1506.2
unnamed: C1506.1, R1522.1, U1506.11
unnamed: C1506.2, R1523.2, U1506.9
unnamed: C1701.1, R1707.2, U1706.3
unnamed: C1701.2, R1704.1, R1706.2
unnamed: C1702.2, R1704.2, R1705.2, U1702.2
unnamed: C1703.1, R1709.1, U1702.11
unnamed: C1703.2, R1710.2, U1702.9
unnamed: C1704.1, R1720.2, U1706.5
unnamed: C1704.2, R1717.1, R1719.2
unnamed: C1705.2, R1717.2, R1718.2, U1708.2
unnamed: C1706.1, R1722.1, U1708.11
unnamed: C1706.2, R1723.2, U1708.9
unnamed: C1801.1, R1807.2, U1706.10
unnamed: C1801.2, R1804.1, R1806.2
unnamed: C1802.2, R1804.2, R1805.2, U1801.2
unnamed: C1803.1, R1809.1, U1801.11
unnamed: C1803.2, R1810.2, U1801.9
unnamed: C1804.1, R1820.2, U1706.12
unnamed: C1804.2, R1817.1, R1819.2
unnamed: C1805.2, R1817.2, R1818.2, U1806.2
unnamed: C1806.1, R1822.1, U1806.11
unnamed: C1806.2, R1823.2, U1806.9
unnamed: C2001.1, R2007.2, U2006.3
unnamed: C2001.2, R2004.1, R2006.2
unnamed: C2002.2, R2004.2, R2005.2, U2002.2
unnamed: C2003.1, R2009.1, U2002.11
unnamed: C2003.2, R2010.2, U2002.9
unnamed: C2004.1, R2020.2, U2006.5
unnamed: C2004.2, R2017.1, R2019.2
unnamed: C2005.2, R2017.2, R2018.2, U2008.2
unnamed: C2006.1, R2022.1, U2008.11
unnamed: C2006.2, R2023.2, U2008.9
unnamed: C2101.1, R2107.2, U2006.10
unnamed: C2101.2, R2104.1, R2106.2
unnamed: C2102.2, R2104.2, R2105.2, U2101.2
unnamed: C2103.1, R2109.1, U2101.11
unnamed: C2103.2, R2110.2, U2101.9
unnamed: C2104.1, R2120.2, U2006.12
unnamed: C2104.2, R2117.1, R2119.2
unnamed: C2105.2, R2117.2, R2118.2, U2106.2
unnamed: C2106.1, R2122.1, U2106.11
unnamed: C2106.2, R2123.2, U2106.9
unnamed: C2301.1, R2307.2, U2306.3
unnamed: C2301.2, R2304.1, R2306.2
unnamed: C2302.2, R2304.2, R2305.2, U2302.2
unnamed: C2303.1, R2309.1, U2302.11
unnamed: C2303.2, R2310.2, U?2302.9
unnamed: C2304.1, R2320.2, U2306.5
unnamed: C2304.2, R2317.1, R2319.2
unnamed: C2305.2, R2317.2, R2318.2, U2308.2
unnamed: C2306.1, R2322.1, U2308.11
unnamed: C2306.2, R2323.2, U2308.9
unnamed: C2401.1, R2407.2, U2306.10
unnamed: C2401.2, R2404.1, R2406.2
unnamed: C2402.2, R2404.2, R2405.2, U2401.2
unnamed: C2403.1, R2409.1, U2401.11
unnamed: C2403.2, R2410.2, U2401.9
unnamed: C2404.1, R2420.2, U2306.12
unnamed: C2404.2, R2417.1, R2419.2
unnamed: C2405.2, R2417.2, R2418.2, U2406.2
unnamed: C2406.1, R2422.1, U2406.11
unnamed: C2406.2, R2423.2, U2406.9
unnamed: C2601.1, R2607.2, U2606.3
unnamed: C2601.2, R2604.1, R2606.2
unnamed: C2602.2, R2604.2, R2605.2, U2602.2
unnamed: C2603.1, R2609.1, U2602.11
unnamed: C2603.2, R2610.2, U2602.9
unnamed: C2604.1, R2620.2, U2606.5
unnamed: C2604.2, R2617.1, R2619.2
unnamed: C2605.2, R2617.2, R2618.2, U2608.2
unnamed: C2606.1, R2622.1, U2608.11
unnamed: C2606.2, R2623.2, U2608.9
unnamed: C2701.1, R2707.2, U2606.10
unnamed: C2701.2, R2704.1, R2706.2
unnamed: C2702.2, R2704.2, R2705.2, U2701.2
unnamed: C2703.1, R2709.1, U2701.11
unnamed: C2703.2, R2710.2, U2701.9
unnamed: C2704.1, R2720.2, U2606.12
unnamed: C2704.2, R2717.1, R2719.2
unnamed: C2705.2, R2717.2, R2718.2, U2706.2
unnamed: C2706.1, R2722.1, U2706.11
unnamed: C2706.2, R2723.2, U2706.9
unnamed: C2901.1, R2907.2, U2906.3
unnamed: C2901.2, R2904.1, R2906.2
unnamed: C2902.2, R2904.2, R2905.2, U2902.2
unnamed: C2903.1, R2909.1, U2902.11
unnamed: C2903.2, R2910.2, U2902.9
unnamed: C2904.1, R2920.2, U2906.5
unnamed: C2904.2, R2917.1, R2919.2
unnamed: C2905.2, R2917.2, R2918.2, U2908.2
unnamed: C2906.1, R2922.1, U2908.11
unnamed: C2906.2, R2923.2, U2908.9
unnamed: C3001.1, R3007.2, U2906.10
unnamed: C3001.2, R3004.1, R3006.2
unnamed: C3002.2, R3004.2, R3005.2, U3001.2
unnamed: C3003.1, R3009.1, U3001.11
unnamed: C3003.2, R3010.2, U3001.9
unnamed: C3004.1, R3020.2, U2906.12
unnamed: C3004.2, R3017.1, R3019.2
unnamed: C3005.2, R3017.2, R3018.2, U3006.2
unnamed: C3006.1, R3022.1, U3006.11
unnamed: C3006.2, R3023.2, U3006.9
unnamed: C3201.1, R3207.2, U3206.3
unnamed: C3201.2, R3204.1, R3206.2
unnamed: C3202.2, R3204.2, R3205.2, U3202.2
unnamed: C3203.1, R3209.1, U3202.11
unnamed: C3203.2, R3210.2, U3202.9
unnamed: C3204.1, R3220.2, U3206.5
unnamed: C3204.2, R3217.1, R3219.2
unnamed: C3205.2, R3217.2, R3218.2, U3208.2
unnamed: C3206.1, R3222.1, U3208.11
unnamed: C3206.2, R3223.2, U3208.9
unnamed: C3301.1, R3307.2, U3206.10
unnamed: C3301.2, R3304.1, R3306.2
unnamed: C3302.2, R3304.2, R3305.2, U3301.2
unnamed: C3303.1, R3309.1, U3301.11
unnamed: C3303.2, R3310.2, U3301.9
unnamed: C3304.1, R3320.2, U3206.12
unnamed: C3304.2, R3317.1, R3319.2
unnamed: C3305.2, R3317.2, R3318.2, U3306.2
unnamed: C3306.1, R3322.1, U3306.11
unnamed: C3306.2, R3323.2, U3306.9
unnamed: C3501.1, R3507.2, U3506.3
unnamed: C3501.2, R3504.1, R3506.2
unnamed: C3502.2, R3504.2, R3505.2, U3502.2
unnamed: C3503.1, R3509.1, U3502.11
unnamed: C3503.2, R3510.2, U3502.9
unnamed: C3504.1, R3520.2, U3506.5
unnamed: C3504.2, R3517.1, R3519.2
unnamed: C3505.2, R3517.2, R3518.2, U3508.2
unnamed: C3506.1, R3522.1, U3508.11
unnamed: C3506.2, R3523.2, U3508.9
unnamed: C3601.1, R3607.2, U3506.10
unnamed: C3601.2, R3604.1, R3606.2
unnamed: C3602.2, R3604.2, R3605.2, U3601.2
unnamed: C3603.1, R3609.1, U3601.11
unnamed: C3603.2, R3610.2, U3601.9
unnamed: C3604.1, R3620.2, U3506.12
unnamed: C3604.2, R3617.1, R3619.2
unnamed: C3605.2, R3617.2, R3618.2, U3606.2
unnamed: C3606.1, R3622.1, U3606.11
unnamed: C3606.2, R3623.2, U?3606.9
unnamed: C3803.1, R3802.2, R3804.1, U3803.1
unnamed: C3804.1, R3805.2, R3807.1, U3805.1
unnamed: C3901.1, C3907.1, U3901.24
unnamed: C3903.1, C3909.1, U3902.24
unnamed: C3913.1, C3915.1, U3901.2
unnamed: C3914.1, C3916.1, U3902.2
unnamed: C3917.2, U3901.3
unnamed: C3918.2, U3902.3
unnamed: C3919.2, U3901.5
unnamed: C3920.2, U3902.5
unnamed: C3921.2, R3905.2, U3901.14
unnamed: C3922.2, R3906.2, U3902.14
unnamed: C3923.1, C3929.1, U3903.24
unnamed: C3925.1, C3931.1, U3904.24
unnamed: C3935.1, C3937.1, U3903.2
unnamed: C3936.1, C3938.1, U3904.2
unnamed: C3939.2, U3903.3
unnamed: C3940.2, U3904.3
unnamed: C3941.2, U3903.5
unnamed: C3942.2, U3904.5
unnamed: C3943.2, R3911.2, U3903.14
unnamed: C3944.2, R3912.2, U3904.14
unnamed: C3945.1, C3948.1, U3905.24
unnamed: C3951.1, C3952.1, U3905.2
unnamed: C3953.2, U3905.3
unnamed: C3954.2, U3905.5
unnamed: C3955.2, R3915.2, U3905.14
unnamed: J701.3, R701.1, U701.12
unnamed: J701.4, U702.1, U703.8, U703.11
unnamed: J701.5, U702.3, U702.8
unnamed: J701.7, U703.2, U703.3
unnamed: J702.3, R715.1, U701.14
unnamed: J702.4, U708.1, U709.8, U709.11
unnamed: J702.5, U708.3, U708.8
unnamed: J702.6, U707.4
unnamed: J702.7, U709.2, U709.3
unnamed: J801.3, R801.1, U701.7
unnamed: J801.4, U801.1, U802.8, U802.11
unnamed: J801.5, U801.3, U801.8
unnamed: J801.7, U802.2, U802.3
unnamed: J802.3, R815.1, U701.9
unnamed: J802.4, U806.1, U807.8, U807.11
unnamed: J802.5, U806.3, U806.8
unnamed: J802.6, U805.4
unnamed: J802.7, U807.2, U807.3
unnamed: J1101.3, R1101.1, U1101.12
unnamed: J1101.4, U1102.1, U1103.8, U1103.11
unnamed: J1101.5, U1102.3, U1102.8
unnamed: J1101.7, U1103.2, U1103.3
unnamed: J1102.3, R1115.1, U1101.14
unnamed: J1102.4, U1108.1, U1109.8, U1109.11
unnamed: J1102.5, U1108.3, U1108.8
unnamed: J1102.6, U1107.4
unnamed: J1102.7, U1109.2, U1109.3
unnamed: J1201.3, R1201.1, U1101.7
unnamed: J1201.4, U1201.1, U1202.8, U1202.11
unnamed: J1201.5, U1201.3, U1201.8
unnamed: J1201.7, U1202.2, U1202.3
unnamed: J1202.3, R1215.1, U1101.9
unnamed: J1202.4, U1206.1, U1207.8, U1207.11
unnamed: J1202.5, U1206.3, U1206.8
unnamed: J1202.6, U1205.4
unnamed: J1202.7, U1207.2, U1207.3
unnamed: J1401.3, R1401.1, U1401.12
unnamed: J1401.4, U1402.1, U1403.8, U1403.11
unnamed: J1401.5, U1402.3, U1402.8
unnamed: J1401.7, U1403.2, U1403.3
unnamed: J1402.3, R1415.1, U1401.14
unnamed: J1402.4, U1408.1, U1409.8, U1409.11
unnamed: J1402.5, U1408.3, U1408.8
unnamed: J1402.6, U1407.4
unnamed: J1402.7, U1409.2, U1409.3
unnamed: J1501.3, R1501.1, U1401.7
unnamed: J1501.4, U1501.1, U1502.8, U1502.11
unnamed: J1501.5, U1501.3, U1501.8
unnamed: J1501.7, U1502.2, U1502.3
unnamed: J1502.3, R1515.1, U1401.9
unnamed: J1502.4, U1506.1, U1507.8, U1507.11
unnamed: J1502.5, U1506.3, U1506.8
unnamed: J1502.6, U1505.4
unnamed: J1502.7, U1507.2, U1507.3
unnamed: J1701.3, R1701.1, U1701.12
unnamed: J1701.4, U1702.1, U1703.8, U1703.11
unnamed: J1701.5, U1702.3, U1702.8
unnamed: J1701.7, U1703.2, U1703.3
unnamed: J1702.3, R1715.1, U1701.14
unnamed: J1702.4, U1708.1, U1709.8, U1709.11
unnamed: J1702.5, U1708.3, U1708.8
unnamed: J1702.6, U1707.4
unnamed: J1702.7, U1709.2, U1709.3
unnamed: J1801.3, R1801.1, U1701.7
unnamed: J1801.4, U1801.1, U1802.8, U1802.11
unnamed: J1801.5, U1801.3, U1801.8
unnamed: J1801.7, U1802.2, U1802.3
unnamed: J1802.3, R1815.1, U1701.9
unnamed: J1802.4, U1806.1, U1807.8, U1807.11
unnamed: J1802.5, U1806.3, U1806.8
unnamed: J1802.6, U1805.4
unnamed: J1802.7, U1807.2, U1807.3
unnamed: J2001.3, R2001.1, U2001.12
unnamed: J2001.4, U2002.1, U2003.8, U2003.11
unnamed: J2001.5, U2002.3, U2002.8
unnamed: J2001.7, U2003.2, U2003.3
unnamed: J2002.3, R2015.1, U2001.14
unnamed: J2002.4, U2008.1, U2009.8, U2009.11
unnamed: J2002.5, U2008.3, U2008.8
unnamed: J2002.6, U2007.4
unnamed: J2002.7, U2009.2, U2009.3
unnamed: J2101.3, R2101.1, U2001.7
unnamed: J2101.4, U2101.1, U2102.8, U2102.11
unnamed: J2101.5, U2101.3, U2101.8
unnamed: J2101.7, U2102.2, U2102.3
unnamed: J2102.3, R2115.1, U2001.9
unnamed: J2102.4, U2106.1, U2107.8, U2107.11
unnamed: J2102.5, U2106.3, U2106.8
unnamed: J2102.6, U2105.4
unnamed: J2102.7, U2107.2, U2107.3
unnamed: J2301.3, R2301.1, U2301.12
unnamed: J2301.4, U2302.1, U2303.8, U2303.11
unnamed: J2301.5, U2302.3, U?2302.8
unnamed: J2301.7, U2303.2, U2303.3
unnamed: J2302.3, R2315.1, U2301.14
unnamed: J2302.4, U2308.1, U2309.8, U2309.11
unnamed: J2302.5, U2308.3, U2308.8
unnamed: J2302.6, U2307.4
unnamed: J2302.7, U2309.2, U2309.3
unnamed: J2401.3, R2401.1, U2301.7
unnamed: J2401.4, U2401.1, U2402.8, U2402.11
unnamed: J2401.5, U2401.3, U2401.8
unnamed: J2401.7, U2402.3, U?2402.2
unnamed: J2402.3, R2415.1, U2301.9
unnamed: J2402.4, U2406.1, U2407.8, U2407.11
unnamed: J2402.5, U2406.3, U2406.8
unnamed: J2402.6, U2405.4
unnamed: J2402.7, U2407.2, U2407.3
unnamed: J2601.3, R2601.1, U2601.12
unnamed: J2601.4, U2602.1, U2603.8, U2603.11
unnamed: J2601.5, U2602.3, U2602.8
unnamed: J2601.7, U2603.2, U2603.3
unnamed: J2602.3, R2615.1, U2601.14
unnamed: J2602.4, U2608.1, U2609.8, U2609.11
unnamed: J2602.5, U2608.3, U2608.8
unnamed: J2602.6, U2607.4
unnamed: J2602.7, U2609.2, U2609.3
unnamed: J2701.3, R2701.1, U2601.7
unnamed: J2701.4, U2701.1, U2702.8, U2702.11
unnamed: J2701.5, U2701.3, U2701.8
unnamed: J2701.7, U2702.2, U2702.3
unnamed: J2702.3, R2715.1, U2601.9
unnamed: J2702.4, U2706.1, U2707.8, U2707.11
unnamed: J2702.5, U2706.3, U2706.8
unnamed: J2702.6, U2705.4
unnamed: J2702.7, U2707.2, U2707.3
unnamed: J2901.3, R2901.1, U2901.12
unnamed: J2901.4, U2902.1, U2903.8, U2903.11
unnamed: J2901.5, U2902.3, U2902.8
unnamed: J2901.7, U2903.2, U2903.3
unnamed: J2902.3, R2915.1, U2901.14
unnamed: J2902.4, U2908.1, U2909.8, U2909.11
unnamed: J2902.5, U2908.3, U2908.8
unnamed: J2902.6, U2907.4
unnamed: J2902.7, U2909.2, U2909.3
unnamed: J3001.3, R3001.1, U2901.7
unnamed: J3001.4, U3001.1, U3002.8, U3002.11
unnamed: J3001.5, U3001.3, U3001.8
unnamed: J3001.7, U3002.2, U3002.3
unnamed: J3002.3, R3015.1, U2901.9
unnamed: J3002.4, U3006.1, U3007.8, U3007.11
unnamed: J3002.5, U3006.3, U3006.8
unnamed: J3002.6, U3005.4
unnamed: J3002.7, U3007.2, U3007.3
unnamed: J3201.3, R3201.1, U3201.12
unnamed: J3201.4, U3202.1, U3203.8, U3203.11
unnamed: J3201.5, U3202.3, U3202.8
unnamed: J3201.7, U3203.2, U3203.3
unnamed: J3202.3, R3215.1, U3201.14
unnamed: J3202.4, U3208.1, U3209.8, U3209.11
unnamed: J3202.5, U3208.3, U3208.8
unnamed: J3202.6, U3207.4
unnamed: J3202.7, U3209.2, U3209.3
unnamed: J3301.3, R3301.1, U3201.7
unnamed: J3301.4, U3301.1, U3302.8, U3302.11
unnamed: J3301.5, U3301.3, U3301.8
unnamed: J3301.7, U3302.2, U3302.3
unnamed: J3302.3, R3315.1, U3201.9
unnamed: J3302.4, U3306.1, U3307.8, U3307.11
unnamed: J3302.5, U3306.3, U3306.8
unnamed: J3302.6, U3305.4
unnamed: J3302.7, U3307.2, U?3307.3
unnamed: J3501.3, R3501.1, U3501.12
unnamed: J3501.4, U3502.1, U3503.8, U3503.11
unnamed: J3501.5, U3502.3, U3502.8
unnamed: J3501.7, U3503.2, U3503.3
unnamed: J3502.3, R3515.1, U3501.14
unnamed: J3502.4, U3508.1, U3509.8, U3509.11
unnamed: J3502.5, U3508.3, U3508.8
unnamed: J3502.6, U3507.4
unnamed: J3502.7, U3509.2, U3509.3
unnamed: J3601.3, R3601.1, U3501.7
unnamed: J3601.4, U3601.1, U3602.8, U3602.11
unnamed: J3601.5, U3601.3, U3601.8
unnamed: J3601.7, U3602.2, U3602.3
unnamed: J3602.3, R3615.1, U3501.9
unnamed: J3602.4, U3606.1, U3607.8, U3607.11
unnamed: J3602.5, U3606.3, U?3606.8
unnamed: J3602.6, U3605.4
unnamed: J3602.7, U3607.2, U3607.3
unnamed: Q3801.1, R3801.1
unnamed: Q3802.1, R3806.1
unnamed: R201.1, U201.4
unnamed: R302.2, U301.32
unnamed: R401.2, U701.15
unnamed: R402.2, U1101.15
unnamed: R403.2, U1401.15
unnamed: R404.2, U1701.15
unnamed: R405.1, U701.6
unnamed: R406.1, U1101.6
unnamed: R407.1, U1401.6
unnamed: R408.1, U1701.6
unnamed: R417.2, U2001.15
unnamed: R418.2, U2301.15
unnamed: R419.2, U2601.15
unnamed: R420.2, U2901.15
unnamed: R421.1, U2001.6
unnamed: R422.1, U2301.6
unnamed: R423.1, U2601.6
unnamed: R424.1, U2901.6
unnamed: R433.2, U3201.15
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
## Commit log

2022-04-02 Initial commit
    One board solution to the Mic tester
2022-04-02 Added CCi and Knowles logos
